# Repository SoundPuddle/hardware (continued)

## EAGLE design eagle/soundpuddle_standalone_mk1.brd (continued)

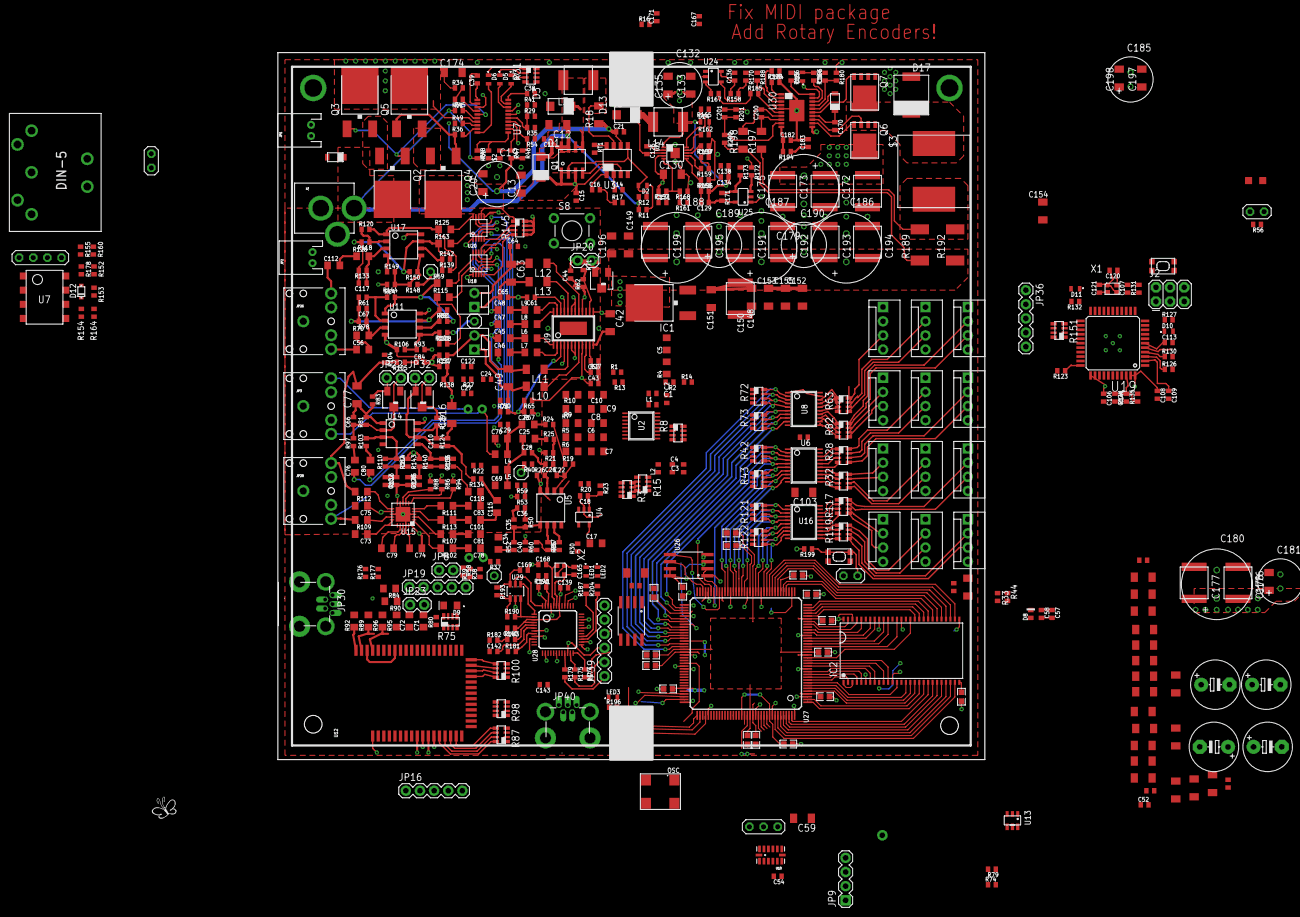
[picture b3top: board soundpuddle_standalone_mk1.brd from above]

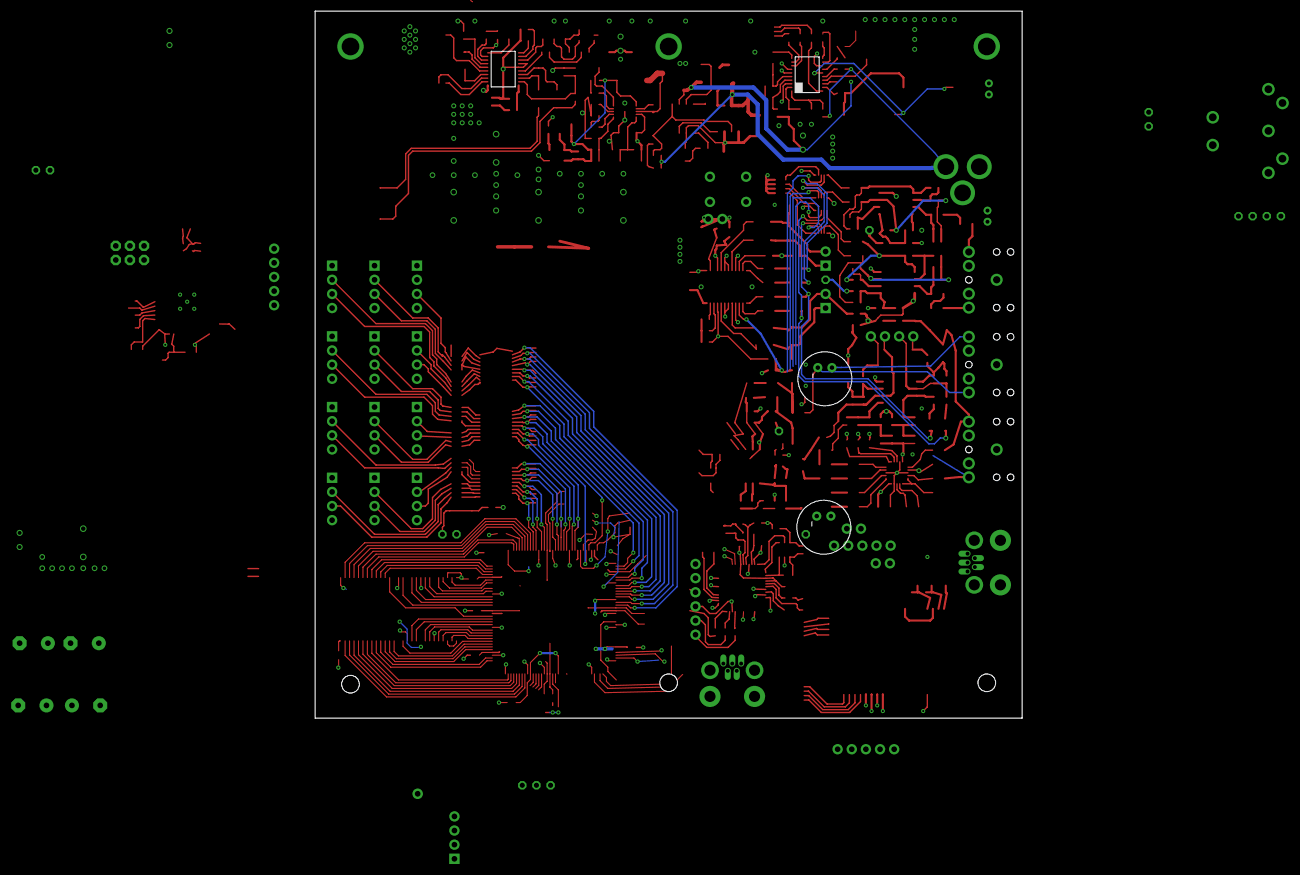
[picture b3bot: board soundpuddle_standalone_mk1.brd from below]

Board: 4 copper layers, 127.0 x 127.0 mm, 531 parts (2 on the bottom side), 427 nets.

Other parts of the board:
U$3: GADGETFACTORY_LOGO

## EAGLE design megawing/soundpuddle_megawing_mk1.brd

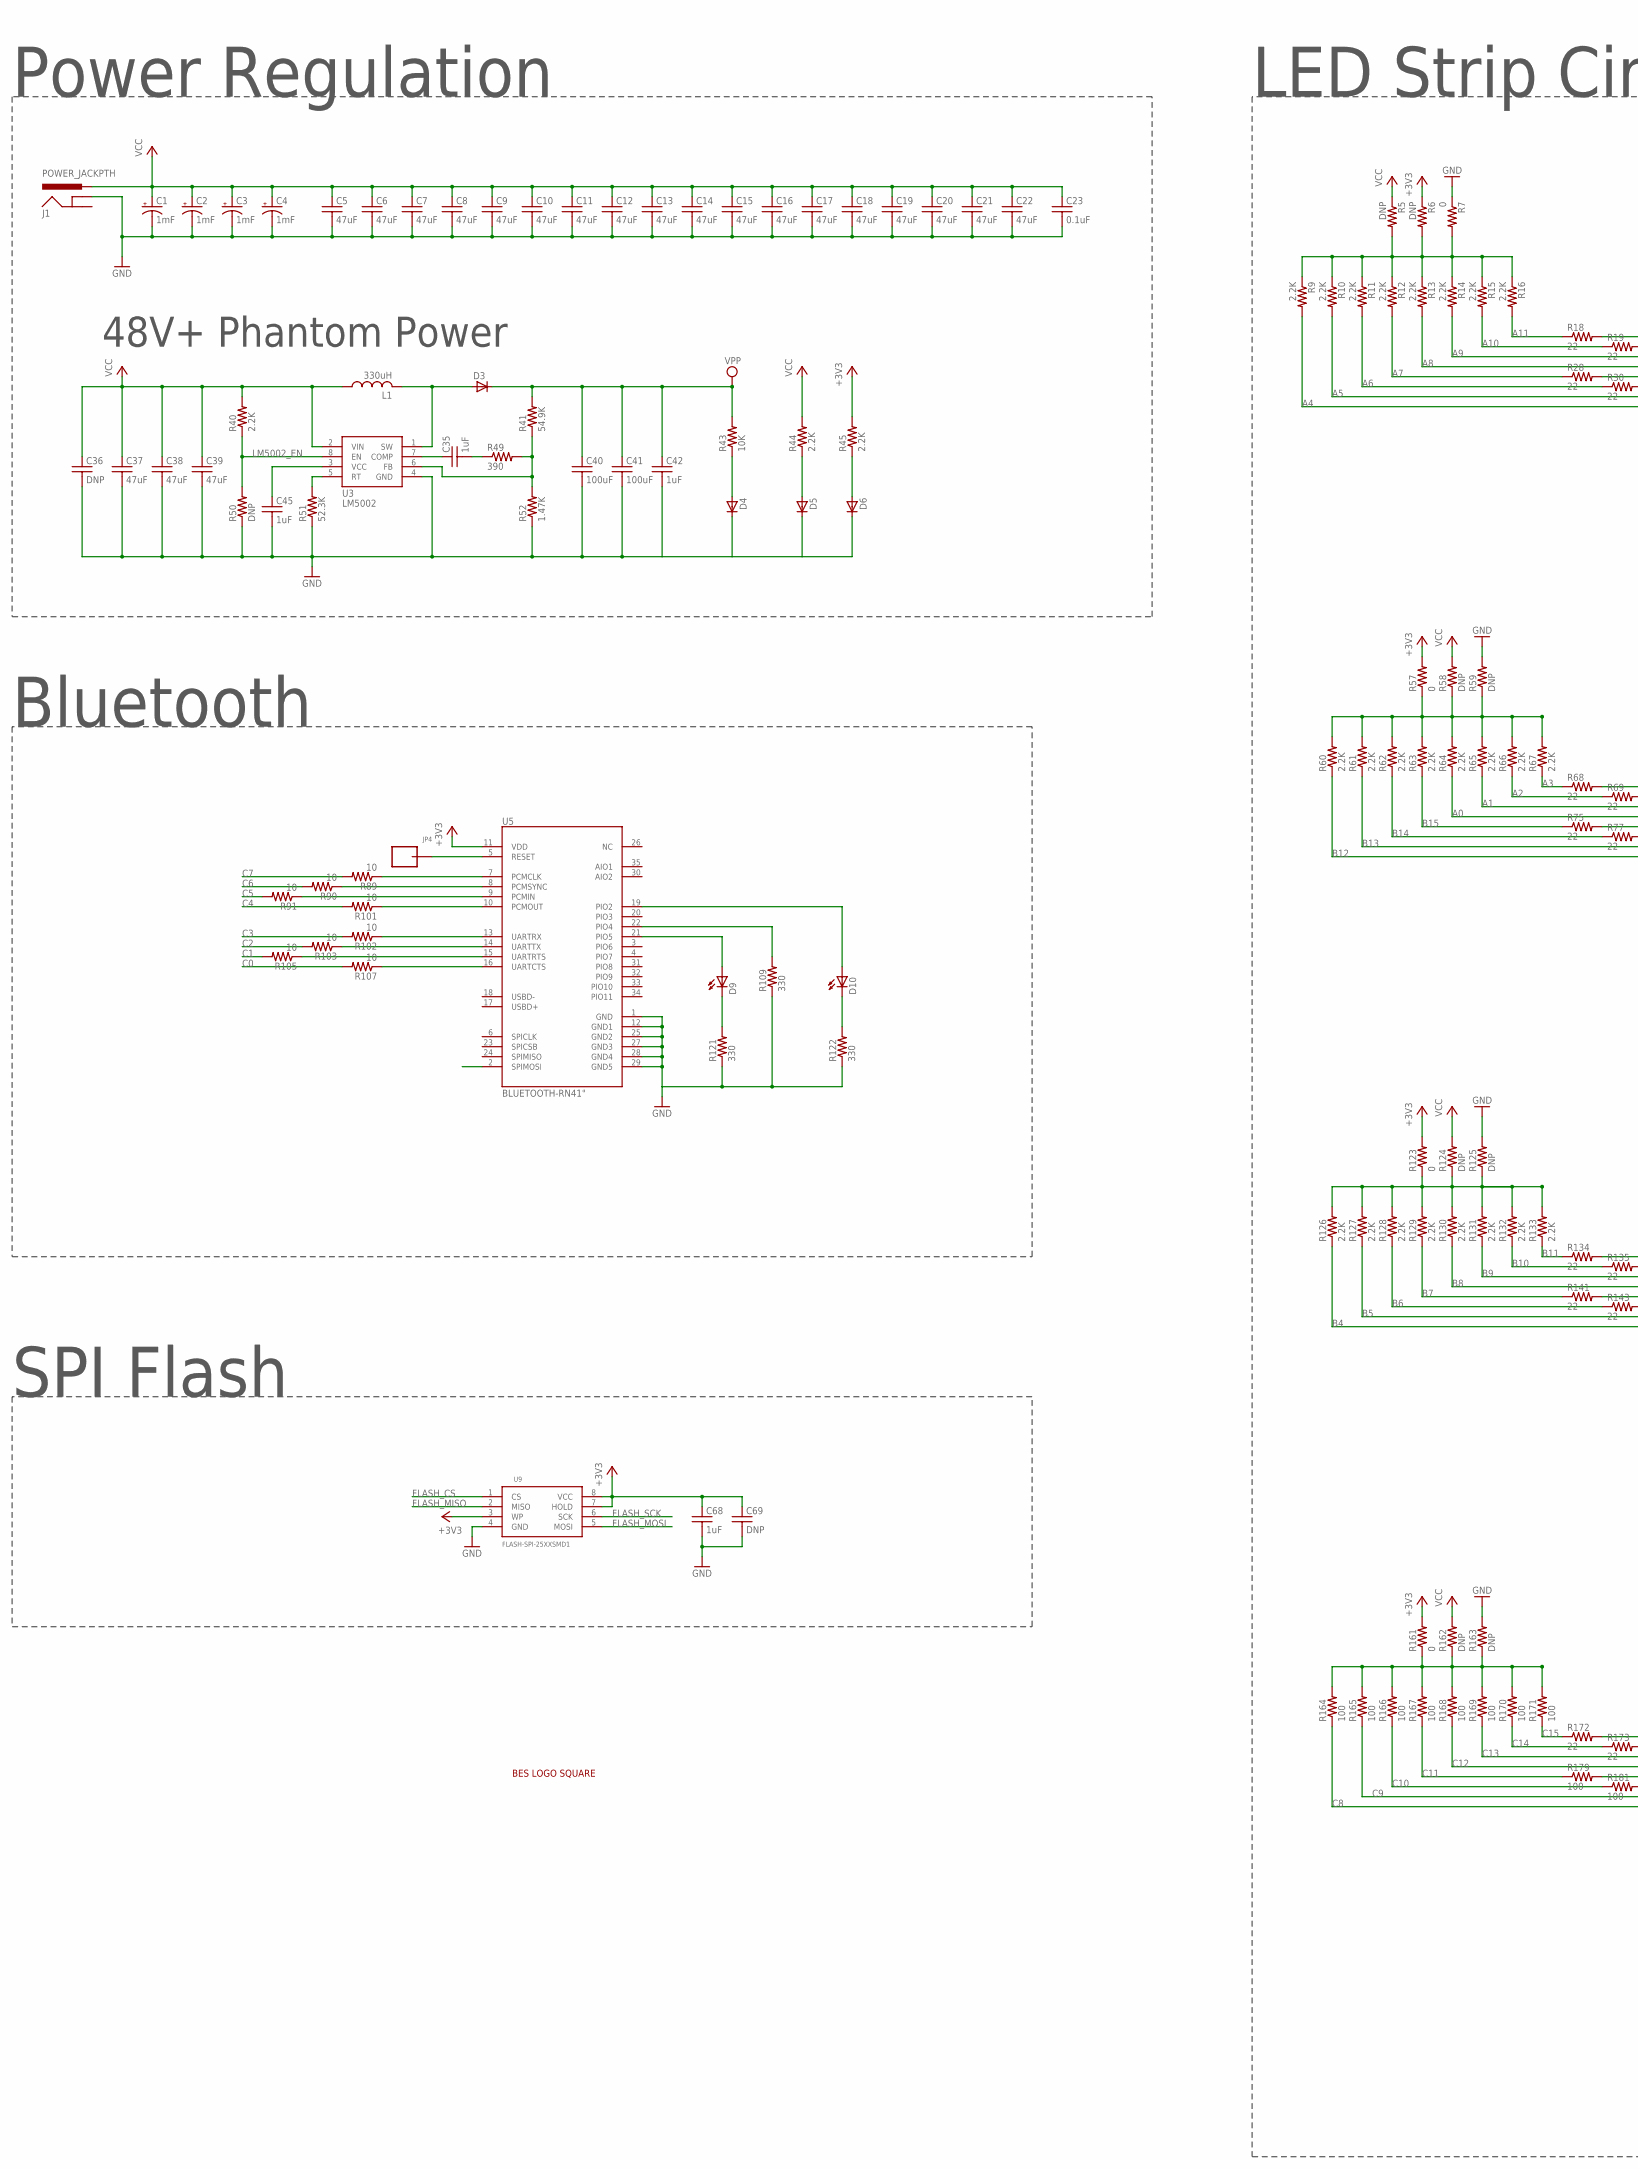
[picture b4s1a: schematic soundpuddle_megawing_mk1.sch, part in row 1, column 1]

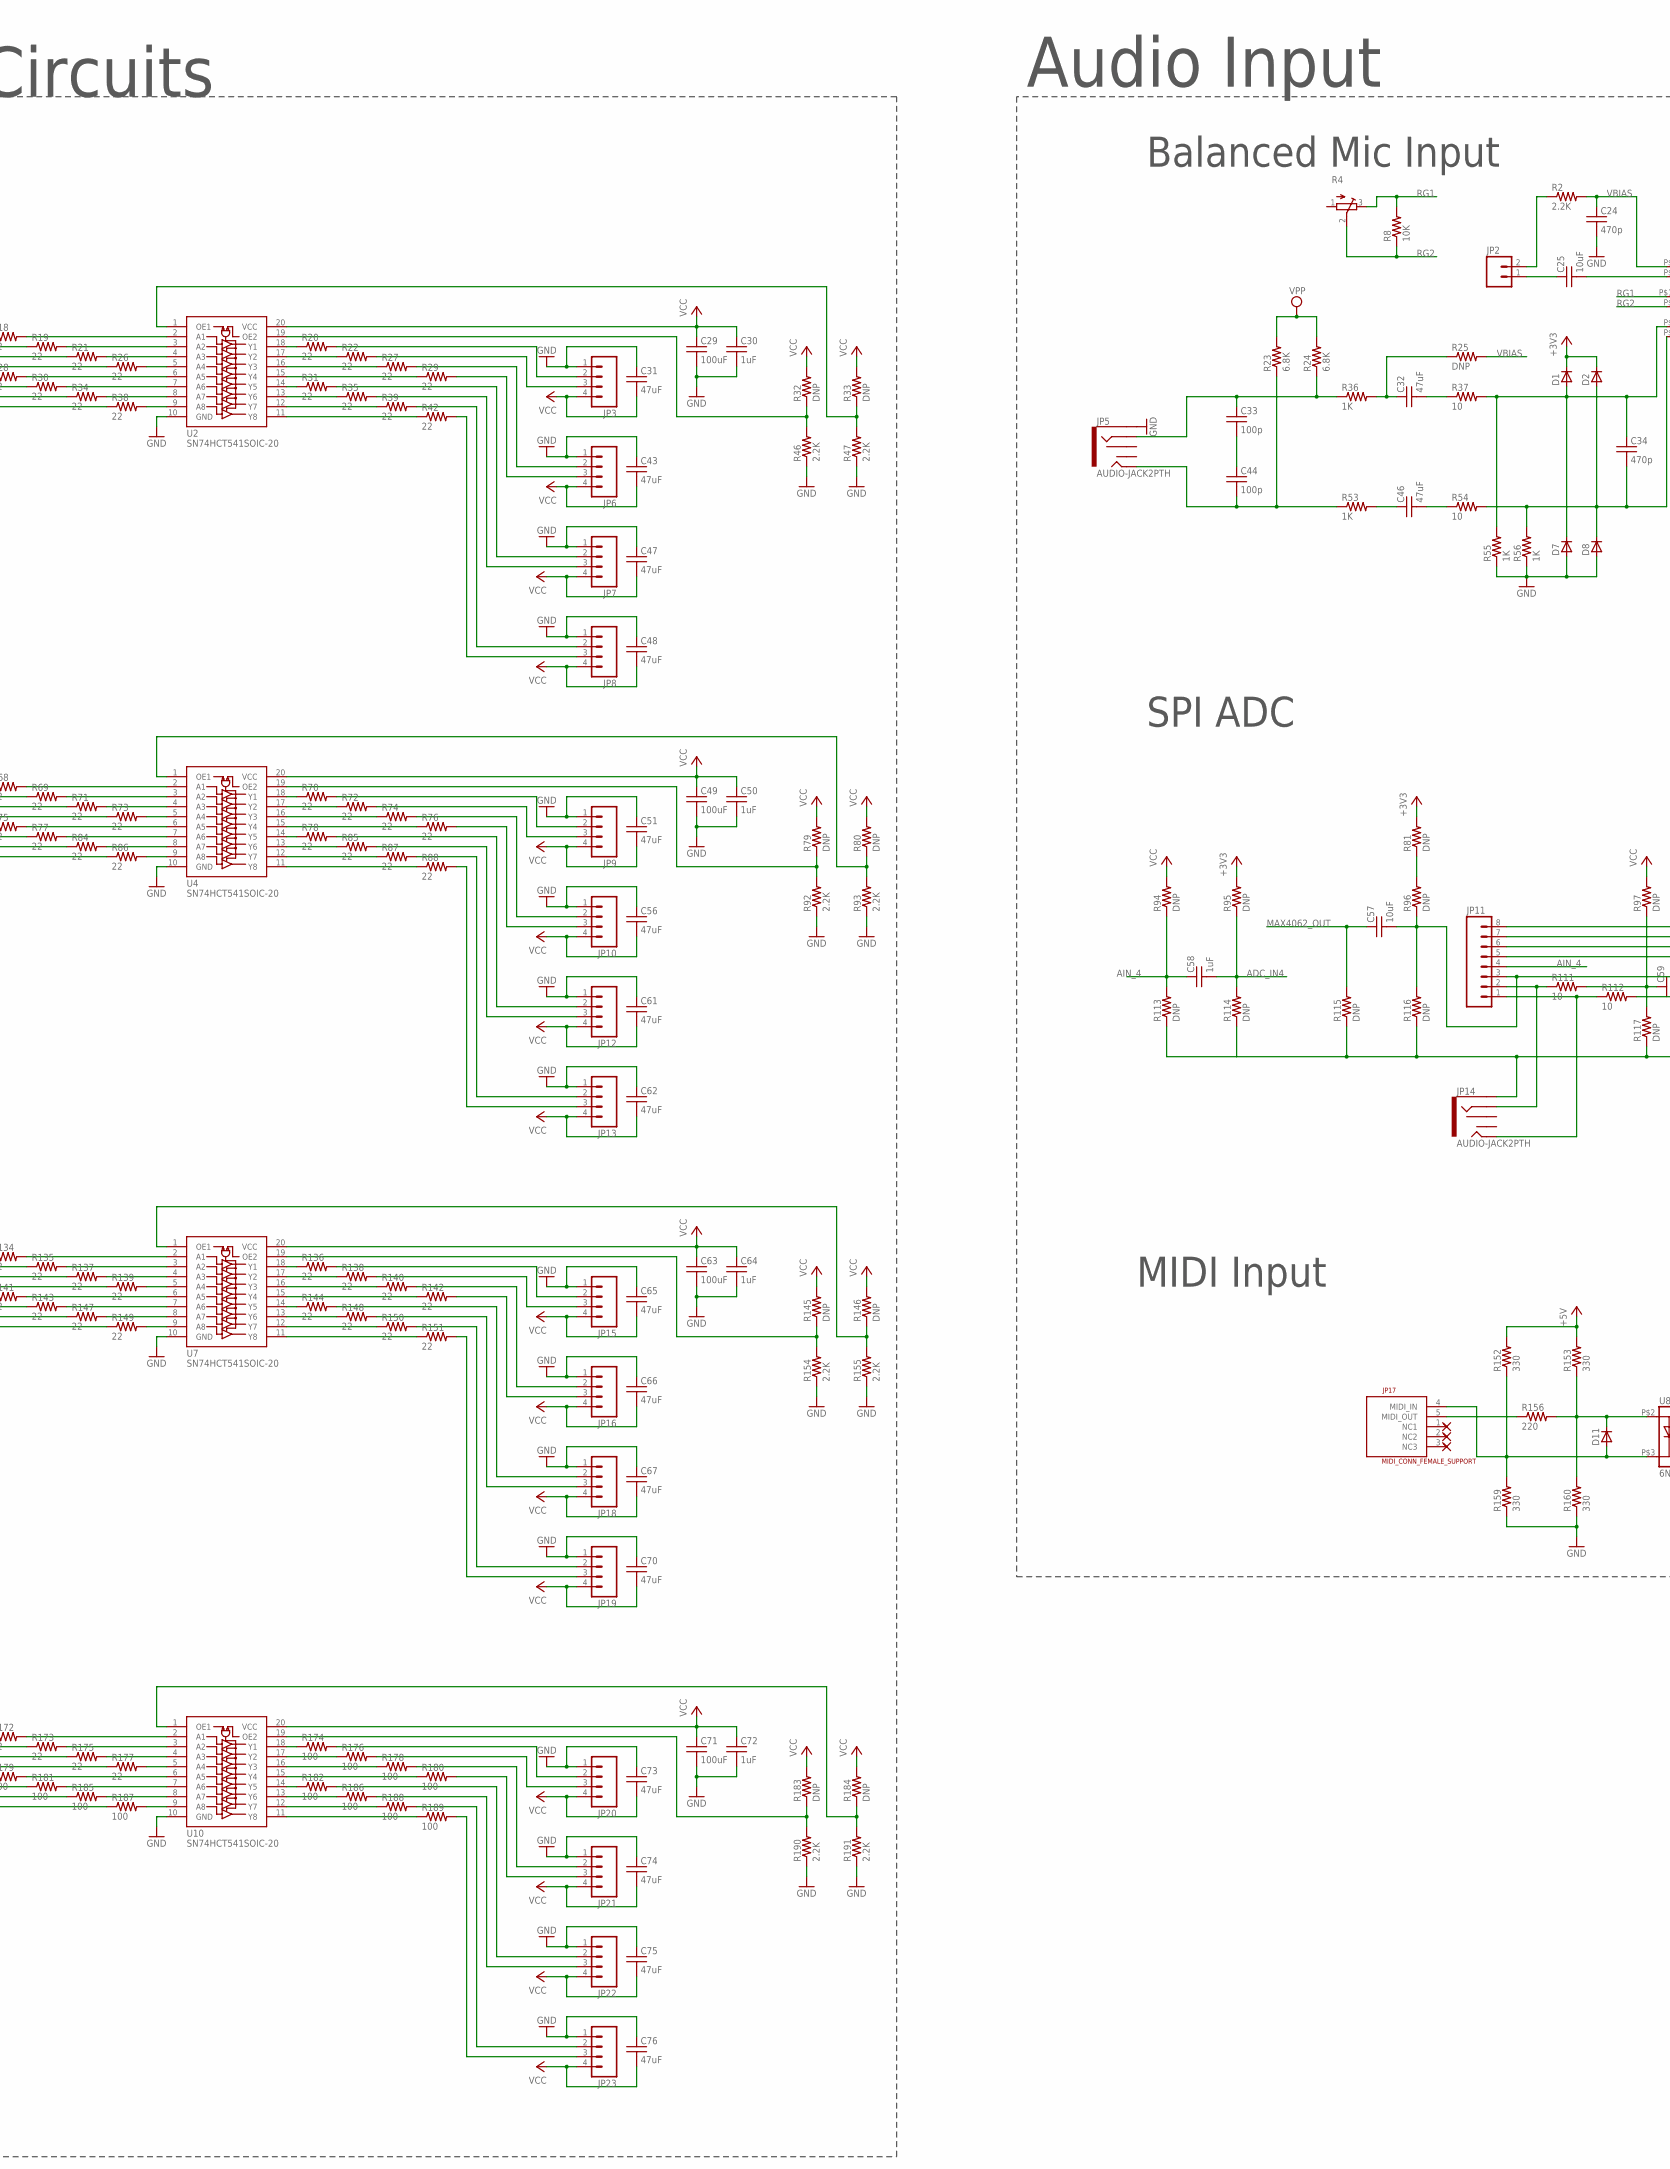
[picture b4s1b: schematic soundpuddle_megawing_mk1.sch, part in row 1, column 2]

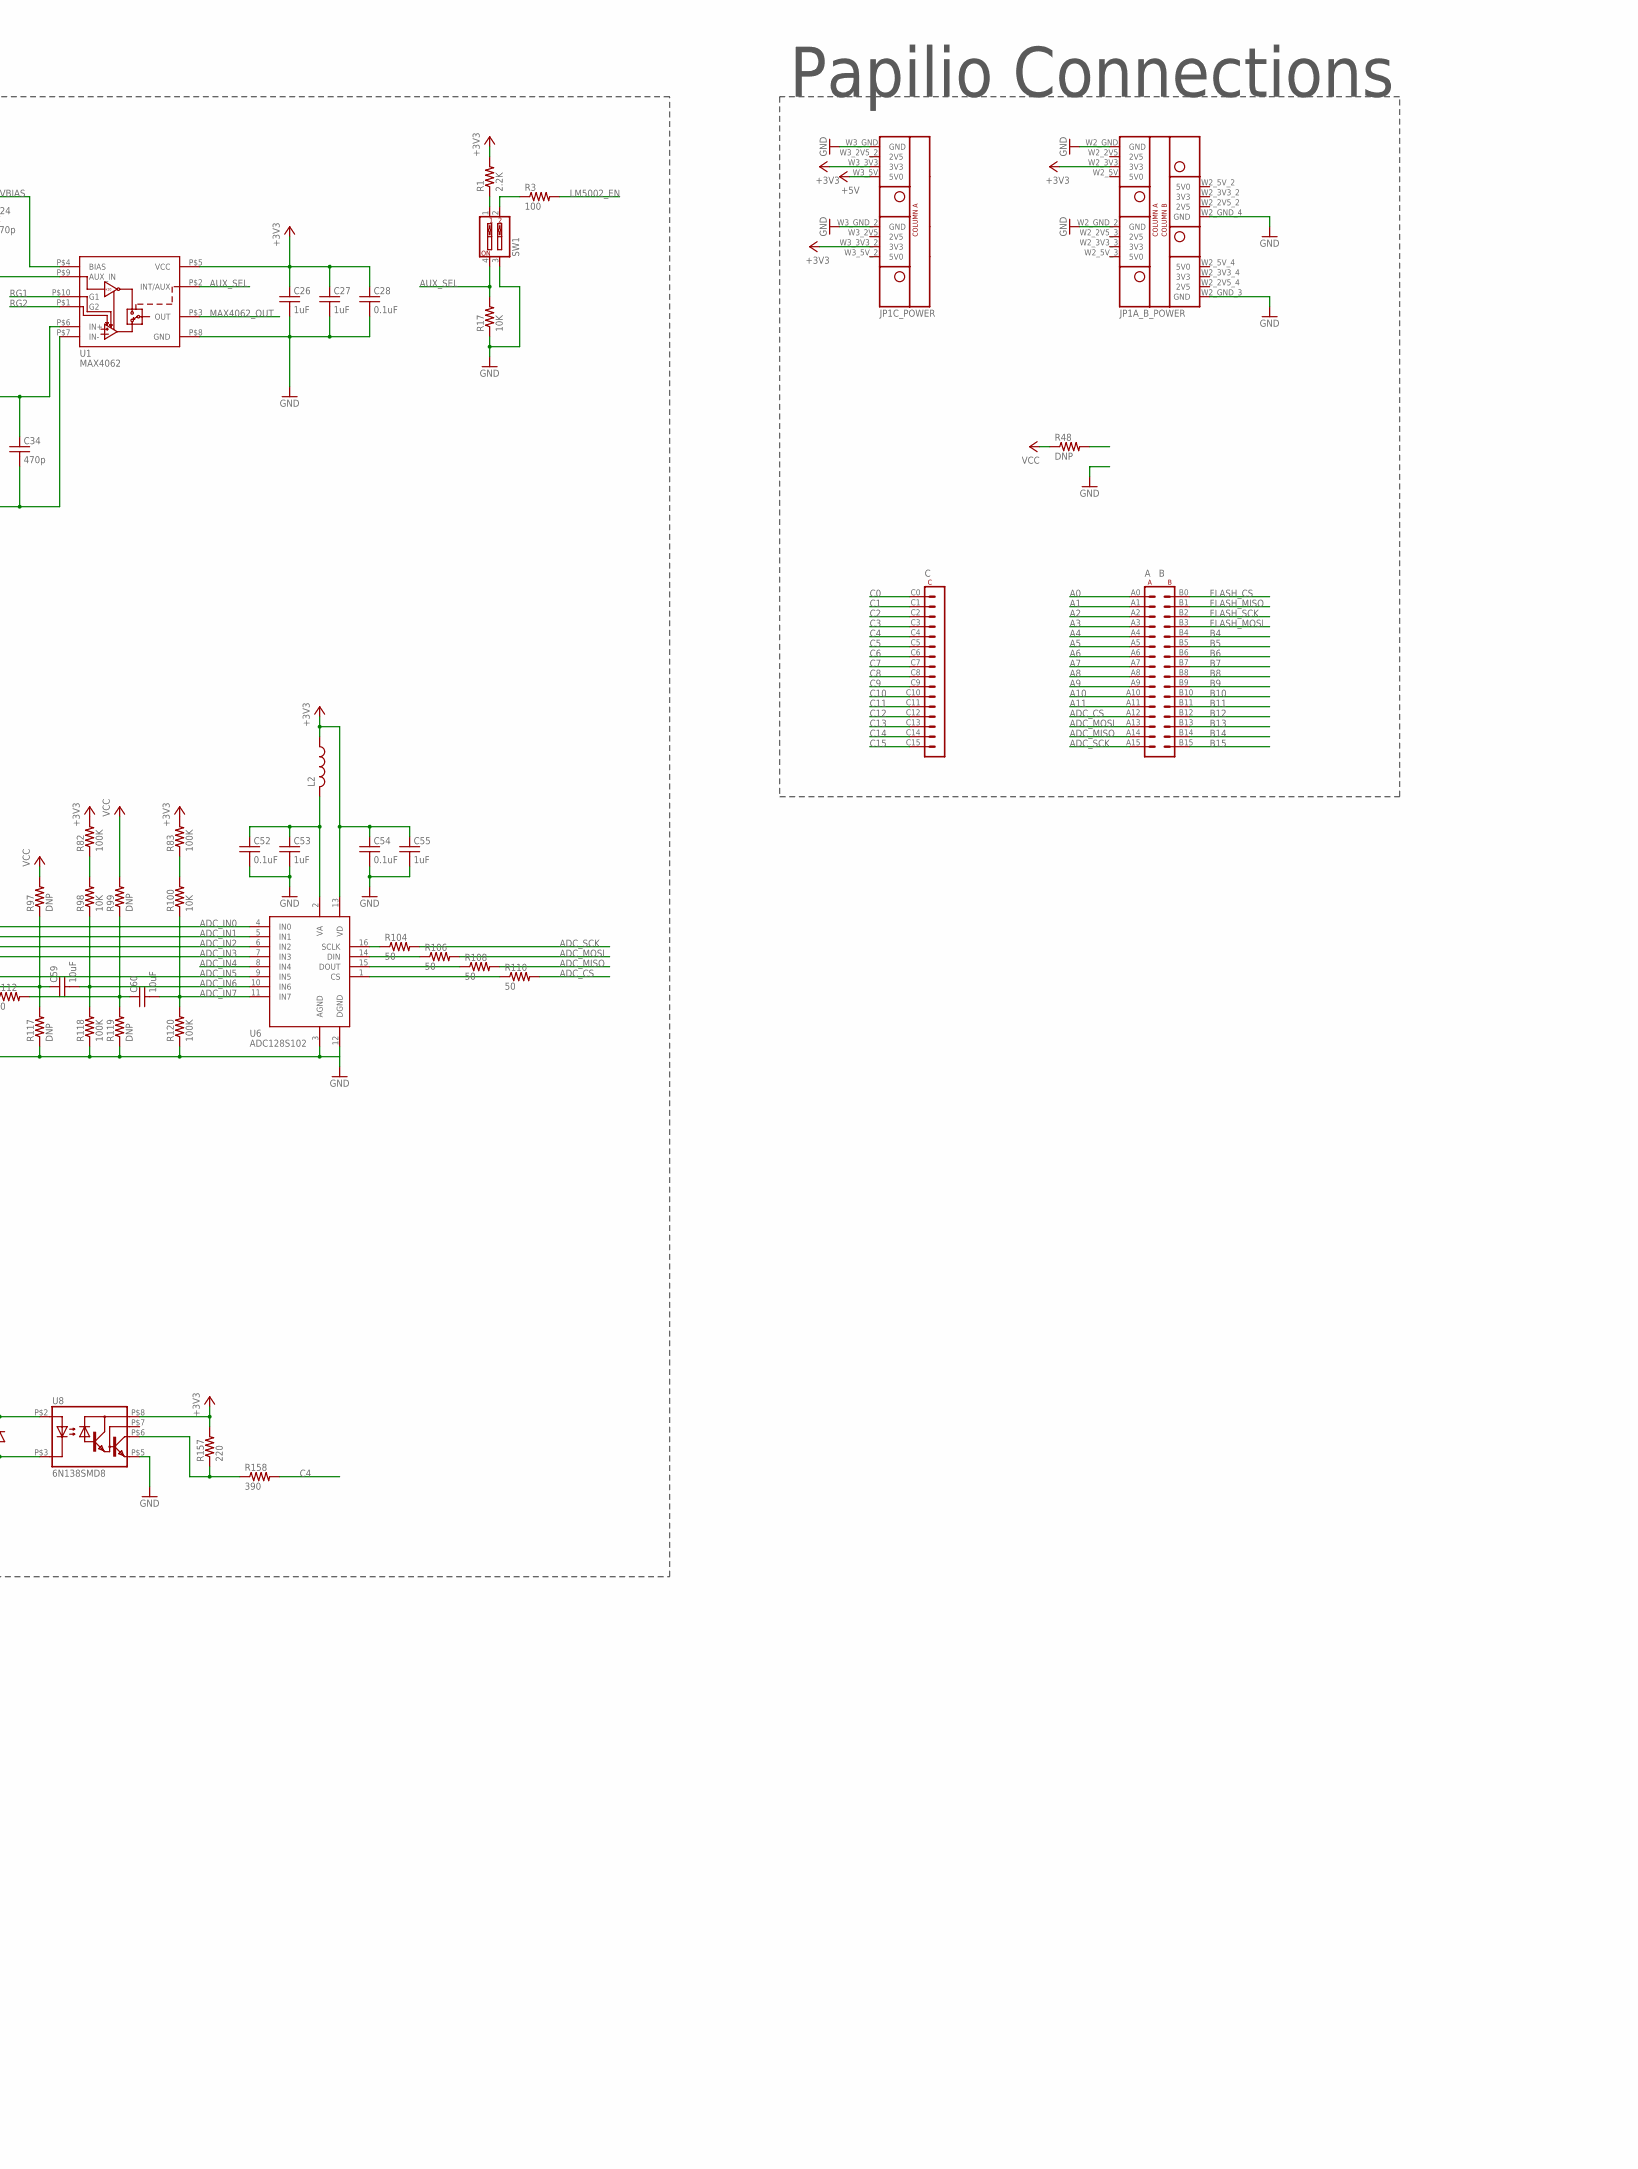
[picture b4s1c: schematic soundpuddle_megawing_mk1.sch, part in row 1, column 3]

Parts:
C1, C2, C3, C4: 1mF; E5-8,5
C5, C6, C7, C8, C9, C10, C11, C12, C13, C14, C15, C16, C17, C18, C19, C20, C21, C22, C31, C32, C37, C38, C39, C43, C46, C47, C48, C51, C56, C61, C62, C65, C66, C67, C70, C73, C74, C75, C76: 47uF; 1206
C23, C28, C52, C54: 0.1uF; 0603
C24, C34: 470p; 0603
C25, C57, C59, C60: 10uF; 0603
C26, C27, C30, C35, C42, C45, C50, C53, C55, C58, C64, C68, C72: 1uF; 0603
C29, C40, C41, C49, C63, C71: 100uF; 1206
C33, C44: 100p; 0603
C36: DNP; 0603
C69: DNP; 1206
D1, D2, D3, D4, D5, D6, D7, D8, D11: DIODE_SMDSOD-323; SOD-323
D9, D10: LED0805; LED_0805
J1: POWER_JACKPTH; POWER_JACK_PTH
JP1: PAPILIO_PLUS_MEGAWING; PAPILIO_PLUS
JP2: M02PTH; 1X02
JP3, JP6, JP7, JP8, JP9, JP10, JP12, JP13, JP15, JP16, JP18, JP19, JP20, JP21, JP22, JP23: M04POLAR; MOLEX-1X4
JP4: HEADER-SMALL-1PIN; HEADER-SMALL-1PIN-0.036IN
JP5, JP14: AUDIO-JACK2PTH; AUDIO-JACK
JP11: M081X08; 1X08
JP17: MIDI_CONN_FEMALE_SUPPORT; DIN_5_FEMALE_SUPPORT
L1: 330uH; INDUCTOR_10X10MM
L2: INDUCTOR0603; 0603
LOGO1: LOGO
R1, R2, R9, R10, R11, R12, R13, R14, R15, R16, R40, R44, R45, R46, R47, R60, R61, R62, R63, R64, R65, R66, R67, R92, R93, R126, R127, R128, R129, R130, R131, R132, R133, R154, R155, R190, R191: 2.2K; 0603
R3, R164, R165, R166, R167, R168, R169, R170, R171, R174, R176, R178, R179, R180, R181, R182, R185, R186, R187, R188, R189: 100; 0603
R4: TRIMPOTTC33X; TC33X
R5, R6, R25, R32, R33, R48, R50, R58, R59, R79, R80, R81, R94, R95, R96, R97, R99, R113, R114, R115, R116, R117, R119, R124, R125, R145, R146, R162, R163, R183, R184: DNP; 0603
R7, R57, R123, R161: 0; 0603
R8, R17, R43, R98, R100: 10K; 0603
R18, R19, R20, R21, R22, R26, R27, R28, R29, R30, R31, R34, R35, R38, R39, R42, R68, R69, R70, R71, R72, R73, R74, R75, R76, R77, R78, R84, R85, R86, R87, R88, R134, R135, R136, R137, R138, R139, R140, R141, R142, R143, R144, R147, R148, R149, R150, R151, R172, R173, R175, R177: 22; 0603
R23, R24: 6.8K; 0603
R36, R53, R55, R56: 1K; 0603
R37, R54, R89, R90, R91, R101, R102, R103, R105, R107, R111, R112: 10; 0603
R41: 54.9K; 0603
R49, R158: 390; 0603
R51: 52.3K; 0603
R52: 1.47K; 0603
R82, R83, R118, R120: 100K; 0603
R104, R106, R108, R110: 50; 0603
R109, R121, R122, R152, R153, R159, R160: 330; 0603
R156, R157: 220; 0603
SW1: SW_DIP-2; DIPSWITCH-02
U1: MAX4062; MSOP10
U2, U4, U7, U10: SN74HCT541SOIC-20; SOIC-20
U3: LM5002; SO8
U5: BLUETOOTH-RN41"; RN41
U6: ADC128S102; TSSOP16
U8: 6N138SMD8; SMD-8
U9: FLASH-SPI-25XXSMD1; SO08-EIAJ

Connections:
+3V3: C26.1, C27.1, C28.1, C54.1, C55.1, C68.1, C69.P$1 (1), D1.C, D2.C, JP1.W2_3V3 (3V3), JP1.W3_3V3 (3V3), JP1.W3_3V3_2 (3V3), L2.1, R1.2, R6.1, R45.2, R57.2, R81.2, R82.2, R83.2, R95.2, R123.2, R157.2, R161.2, U1.P$5 (VCC), U5.11 (VDD), U6.13 (VD), U8.P$8 (VCC), U9.3 (WP), U9.7 (HOLD), U9.8 (VCC)
+5V: JP1.W3_5V (5V0), R152.2, R153.2
A0: JP1.A0, R64.1, R73.1
A1: JP1.A1, R65.1, R71.1
A2: JP1.A2, R66.1, R69.1
A3: JP1.A3, R67.1, R68.1
A4: JP1.A4, R9.2, R38.1
A5: JP1.A5, R10.2, R34.1
A6: JP1.A6, R11.2, R30.1
A7: JP1.A7, R12.2, R28.1
A8: JP1.A8, R13.2, R26.1
A9: JP1.A9, R14.2, R21.1
A10: JP1.A10, R15.2, R19.1
A11: JP1.A11, R16.2, R18.1
ADC_CS: JP1.A12, R110.2
ADC_IN0: JP11.8, U6.4 (IN0)
ADC_IN1: JP11.7, U6.5 (IN1)
ADC_IN2: JP11.6, U6.6 (IN2)
ADC_IN3: JP11.5, U6.7 (IN3)
ADC_IN4: C58.2, R95.1, R114.2, U6.8 (IN4)
ADC_IN5: C57.2, JP11.3, R96.1, R116.2, U6.9 (IN5)
ADC_IN6: C59.2, R98.1, R118.2, U6.10 (IN6)
ADC_IN7: C60.2, R100.1, R120.2, U6.11 (IN7)
ADC_MISO: JP1.A14, R108.2
ADC_MOSI: JP1.A13, R106.2
ADC_SCK: JP1.A15, R104.2
AIN_4: C58.1, JP11.4, R94.1, R113.2
AUX_SEL: R17.2, SW1.4, U1.P$2 (INT/AUX)
B4: JP1.B4, R126.1, R149.1
B5: JP1.B5, R127.1, R147.1
B6: JP1.B6, R128.1, R143.1
B7: JP1.B7, R129.1, R141.1
B8: JP1.B8, R130.1, R139.1
B9: JP1.B9, R131.1, R137.1
B10: JP1.B10, R132.1, R135.1
B11: JP1.B11, R133.1, R134.1
B12: JP1.B12, R60.1, R86.1
B13: JP1.B13, R61.1, R84.1
B14: JP1.B14, R62.1, R77.1
B15: JP1.B15, R63.1, R75.1
C0: JP1.C0, R107.2
C1: JP1.C1, R105.2
C2: JP1.C2, R103.2
C3: JP1.C3, R102.2
C4: JP1.C4, R101.2, R158.2
C5: JP1.C5, R91.2
C6: JP1.C6, R90.2
C7: JP1.C7, R89.2
C8: JP1.C8, R164.1, R187.1
C9: JP1.C9, R165.1, R185.1
C10: JP1.C10, R166.1, R181.1
C11: JP1.C11, R167.1, R179.1
C12: JP1.C12, R168.1, R177.1
C13: JP1.C13, R169.1, R175.1
C14: JP1.C14, R170.1, R173.1
C15: JP1.C15, R171.1, R172.1
FLASH_CS: JP1.B0, U9.1 (CS)
FLASH_MISO: JP1.B1, U9.2 (MISO)
FLASH_MOSI: JP1.B3, U9.5 (MOSI)
FLASH_SCK: JP1.B2, U9.6 (SCK)
GND: C1.-, C2.-, C3.-, C4.-, C5.P$2 (2), C6.P$2 (2), C7.P$2 (2), C8.P$2 (2), C9.P$2 (2), C10.P$2 (2), C11.P$2 (2), C12.P$2 (2), C13.P$2 (2), C14.P$2 (2), C15.P$2 (2), C16.P$2 (2), C17.P$2 (2), C18.P$2 (2), C19.P$2 (2), C20.P$2 (2), C21.P$2 (2), C22.P$2 (2), C23.2, C24.2, C26.2, C27.2, C28.2, C29.P$2 (2), C30.2, C31.P$1 (1), C36.2, C37.P$2 (2), C38.P$2 (2), C39.P$2 (2), C40.P$2 (2), C41.P$2 (2), C42.2, C43.P$1 (1), C45.2, C47.P$1 (1), C48.P$1 (1), C49.P$2 (2), C50.2, C51.P$1 (1), C52.2, C53.2, C54.2, C55.2, C56.P$1 (1), C61.P$1 (1), C62.P$1 (1), C63.P$2 (2), C64.2, C65.P$1 (1), C66.P$1 (1), C67.P$1 (1), C68.2, C69.P$2 (2), C70.P$1 (1), C71.P$2 (2), C72.2, C73.P$1 (1), C74.P$1 (1), C75.P$1 (1), C76.P$1 (1), D4.C, D5.C, D6.C, D7.A, D8.A, J1.GNDBREAK, JP1.W2_GND (GND), JP1.W2_GND_2 (GND), JP1.W2_GND_3 (GND), JP1.W2_GND_4 (GND), JP1.W3_GND (GND), JP1.W3_GND_2 (GND), JP3.1, JP5.SLEEVE, JP6.1, JP7.1, JP8.1, JP9.1, JP10.1, JP12.1, JP13.1, JP14.SLEEVE, JP15.1, JP16.1, JP18.1, JP19.1, JP20.1, JP21.1, JP22.1, JP23.1, R7.1, R17.1, R46.1, R47.1, R50.1, R51.1, R52.1, R55.1, R56.1, R59.2, R92.1, R93.1, R109.1, R113.1, R114.1, R115.1, R116.1, R117.1, R118.1, R119.1, R120.1, R121.1, R122.1, R125.2, R154.1, R155.1, R159.1, R160.1, R163.2, R190.1, R191.1, SW1.3, U1.P$8 (GND), U2.10 (GND), U3.4 (GND), U4.10 (GND), U5.1 (GND), U5.12 (GND1), U5.25 (GND2), U5.27 (GND3), U5.28 (GND4), U5.29 (GND5), U6.3 (AGND), U6.12 (DGND), U7.10 (GND), U8.P$5 (GND), U9.4 (GND), U10.10 (GND)
LM5002_EN: R3.2, R40.1, R50.2, U3.8 (EN)
MAX4062_OUT: C57.1, R115.2, U1.P$3 (OUT)
unnamed: C52.1, C53.1, L2.2, U6.2 (VA)
unnamed: R107.1, U5.16 (UARTCTS)
unnamed: JP2.2, R2.1
unnamed: C25.1, JP2.1
unnamed: R105.1, U5.15 (UARTRTS)
unnamed: R103.1, U5.14 (UARTTX)
unnamed: C46.P$1 (1), R53.2
unnamed: C44.2, JP5.TIP, R23.1, R53.1
unnamed: C33.2, C44.1
unnamed: C32.P$1 (1), R25.1, R36.2
unnamed: R102.1, U5.13 (UARTRX)
unnamed: R104.1, U6.16 (SCLK)
unnamed: R106.1, U6.14 (DIN)
unnamed: R110.1, U6.1 (CS)
unnamed: R108.1, U6.15 (DOUT)
unnamed: D9.2 (C), R121.2
unnamed: D10.2 (C), R122.2
unnamed: D10.1 (A), U5.19 (PIO2)
unnamed: D9.1 (A), U5.21 (PIO5)
unnamed: D3.A, L1.P$2 (2), U3.1 (SW)
unnamed: R109.2, U5.22 (PIO4)
unnamed: JP20.3, R176.2
unnamed: R1.1, SW1.1
unnamed: R33.1, R47.2, U2.1 (OE1)
unnamed: R5.2, R6.2, R7.2, R9.1, R10.1, R11.1, R12.1, R13.1, R14.1, R15.1, R16.1
unnamed: C32.P$2 (2), R37.1
unnamed: C46.P$2 (2), R54.1
unnamed: D4.A, R43.1
unnamed: D5.A, R44.1
unnamed: R81.1, R96.2
unnamed: R82.1, R98.2
unnamed: JP11.2, JP14.RING, R111.1
unnamed: R83.1, R100.2
unnamed: JP11.1, JP14.TIP, R112.1
unnamed: C60.1, R99.1, R112.2, R119.2
unnamed: C59.1, R97.1, R111.2, R117.2
unnamed: R3.1, SW1.2
unnamed: R161.1, R162.1, R163.1, R164.2, R165.2, R166.2, R167.2, R168.2, R169.2, R170.2, R171.2
unnamed: R101.1, U5.10 (PCMOUT)
unnamed: D6.A, R45.1
unnamed: R79.1, R92.2, U4.19 (OE2)
unnamed: R145.1, R154.2, U7.19 (OE2)
unnamed: R184.1, R191.2, U10.1 (OE1)
unnamed: R91.1, U5.9 (PCMIN)
unnamed: R90.1, U5.8 (PCMSYNC)
unnamed: R89.1, U5.7 (PCMCLK)
unnamed: R183.1, R190.2, U10.19 (OE2)
unnamed: JP4.P$1, U5.5 (RESET)
unnamed: JP17.5 (MIDI_OUT), R156.1
unnamed: D11.C, R153.1, R156.2, R160.2, U8.P$2 (A)
unnamed: D11.A, JP17.4 (MIDI_IN), R152.1, R159.2, U8.P$3 (C)
unnamed: R32.1, R46.2, U2.19 (OE2)
unnamed: R19.2, U2.3 (A2)
unnamed: R26.2, U2.5 (A4)
unnamed: R18.2, U2.2 (A1)
unnamed: R157.1, R158.1, U8.P$6 (VO)
unnamed: R21.2, U2.4 (A3)
unnamed: R28.2, U2.6 (A5)
unnamed: R30.2, U2.7 (A6)
unnamed: R34.2, U2.8 (A7)
unnamed: R38.2, U2.9 (A8)
unnamed: R31.1, U2.14 (Y5)
unnamed: R20.1, U2.18 (Y1)
unnamed: R22.1, U2.17 (Y2)
unnamed: R27.1, U2.16 (Y3)
unnamed: R29.1, U2.15 (Y4)
unnamed: R35.1, U2.13 (Y6)
unnamed: R39.1, U2.12 (Y7)
unnamed: R42.1, U2.11 (Y8)
unnamed: JP7.2, R31.2
unnamed: JP7.3, R35.2
unnamed: JP8.2, R39.2
unnamed: JP8.3, R42.2
unnamed: JP6.3, R29.2
unnamed: JP6.2, R27.2
unnamed: JP3.3, R22.2
unnamed: JP3.2, R20.2
unnamed: JP13.2, R87.2
unnamed: R51.2, U3.5 (RT)
unnamed: C45.1, U3.3 (VCC)
unnamed: C35.1, U3.7 (COMP)
unnamed: R41.1, R49.2, R52.2, U3.6 (FB)
unnamed: C35.2, R49.1
unnamed: C34.2, D2.A, D8.C, R54.2, R56.2, U1.P$7 (IN-)
unnamed: C25.2, U1.P$9 (AUX_IN)
unnamed: R80.1, R93.2, U4.1 (OE1)
unnamed: C33.1, JP5.RING, R24.1, R36.1
unnamed: C34.1, D1.A, D7.C, R37.2, R55.2, U1.P$6 (IN+)
unnamed: R68.2, U4.2 (A1)
unnamed: R69.2, U4.3 (A2)
unnamed: R73.2, U4.5 (A4)
unnamed: R71.2, U4.4 (A3)
unnamed: R75.2, U4.6 (A5)
unnamed: R77.2, U4.7 (A6)
unnamed: R84.2, U4.8 (A7)
unnamed: R86.2, U4.9 (A8)
unnamed: R57.1, R58.1, R59.1, R60.2, R61.2, R62.2, R63.2, R64.2, R65.2, R66.2, R67.2
unnamed: R78.1, U4.14 (Y5)
unnamed: R70.1, U4.18 (Y1)
unnamed: R72.1, U4.17 (Y2)
unnamed: R74.1, U4.16 (Y3)
unnamed: R76.1, U4.15 (Y4)
unnamed: R85.1, U4.13 (Y6)
unnamed: R87.1, U4.12 (Y7)
unnamed: R88.1, U4.11 (Y8)
unnamed: JP12.2, R78.2
unnamed: JP12.3, R85.2
unnamed: JP13.3, R88.2
unnamed: JP23.2, R188.2
unnamed: JP10.3, R76.2
unnamed: JP10.2, R74.2
unnamed: JP9.3, R72.2
unnamed: JP9.2, R70.2
unnamed: R146.1, R155.2, U7.1 (OE1)
unnamed: R134.2, U7.2 (A1)
unnamed: R135.2, U7.3 (A2)
unnamed: R139.2, U7.5 (A4)
unnamed: R137.2, U7.4 (A3)
unnamed: R141.2, U7.6 (A5)
unnamed: R143.2, U7.7 (A6)
unnamed: R147.2, U7.8 (A7)
unnamed: R149.2, U7.9 (A8)
unnamed: R123.1, R124.1, R125.1, R126.2, R127.2, R128.2, R129.2, R130.2, R131.2, R132.2, R133.2
unnamed: R144.1, U7.14 (Y5)
unnamed: R136.1, U7.18 (Y1)
unnamed: R138.1, U7.17 (Y2)
unnamed: R140.1, U7.16 (Y3)
unnamed: R142.1, U7.15 (Y4)
unnamed: R148.1, U7.13 (Y6)
unnamed: R150.1, U7.12 (Y7)
unnamed: R151.1, U7.11 (Y8)
unnamed: JP18.2, R144.2
unnamed: JP18.3, R148.2
unnamed: JP19.2, R150.2
unnamed: JP19.3, R151.2
unnamed: JP16.3, R142.2
unnamed: JP16.2, R140.2
unnamed: JP15.3, R138.2
unnamed: JP15.2, R136.2
unnamed: R172.2, U10.2 (A1)
unnamed: R173.2, U10.3 (A2)
unnamed: R177.2, U10.5 (A4)
unnamed: R175.2, U10.4 (A3)
unnamed: R179.2, U10.6 (A5)
unnamed: R181.2, U10.7 (A6)
unnamed: R185.2, U10.8 (A7)
unnamed: R187.2, U10.9 (A8)
unnamed: R182.1, U10.14 (Y5)
unnamed: R174.1, U10.18 (Y1)
unnamed: R176.1, U10.17 (Y2)
unnamed: R178.1, U10.16 (Y3)
unnamed: R180.1, U10.15 (Y4)
unnamed: R186.1, U10.13 (Y6)
unnamed: R188.1, U10.12 (Y7)
unnamed: R189.1, U10.11 (Y8)
unnamed: JP22.2, R182.2
unnamed: JP22.3, R186.2
unnamed: JP23.3, R189.2
unnamed: JP21.3, R180.2
unnamed: JP21.2, R178.2
unnamed: JP20.2, R174.2
RG1: R4.3 (E), R8.2, U1.P$10 (G1)
RG2: R4.2 (S), R8.1, U1.P$1 (G2)
VBIAS: C24.1, R2.2, R25.2, U1.P$4 (BIAS)
VCC: C1.+, C2.+, C3.+, C4.+, C5.P$1 (1), C6.P$1 (1), C7.P$1 (1), C8.P$1 (1), C9.P$1 (1), C10.P$1 (1), C11.P$1 (1), C12.P$1 (1), C13.P$1 (1), C14.P$1 (1), C15.P$1 (1), C16.P$1 (1), C17.P$1 (1), C18.P$1 (1), C19.P$1 (1), C20.P$1 (1), C21.P$1 (1), C22.P$1 (1), C23.1, C29.P$1 (1), C30.1, C31.P$2 (2), C36.1, C37.P$1 (1), C38.P$1 (1), C39.P$1 (1), C43.P$2 (2), C47.P$2 (2), C48.P$2 (2), C49.P$1 (1), C50.1, C51.P$2 (2), C56.P$2 (2), C61.P$2 (2), C62.P$2 (2), C63.P$1 (1), C64.1, C65.P$2 (2), C66.P$2 (2), C67.P$2 (2), C70.P$2 (2), C71.P$1 (1), C72.1, C73.P$2 (2), C74.P$2 (2), C75.P$2 (2), C76.P$2 (2), J1.PWR, JP3.4, JP6.4, JP7.4, JP8.4, JP9.4, JP10.4, JP12.4, JP13.4, JP15.4, JP16.4, JP18.4, JP19.4, JP20.4, JP21.4, JP22.4, JP23.4, L1.P$1 (1), R5.1, R32.2, R33.2, R40.2, R44.2, R48.1, R58.2, R79.2, R80.2, R94.2, R97.2, R99.2, R124.2, R145.2, R146.2, R162.2, R183.2, R184.2, U2.20 (VCC), U3.2 (VIN), U4.20 (VCC), U7.20 (VCC), U10.20 (VCC)
VPP: C40.P$1 (1), C41.P$1 (1), C42.1, D3.C, R23.2, R24.2, R41.2, R43.2

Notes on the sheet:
Audio Input
Papilio Connections
LED Strip Circuits
Bluetooth
Power Regulation
SPI Flash
48V+ Phantom Power
MIDI Input
SPI ADC
Balanced Mic Input

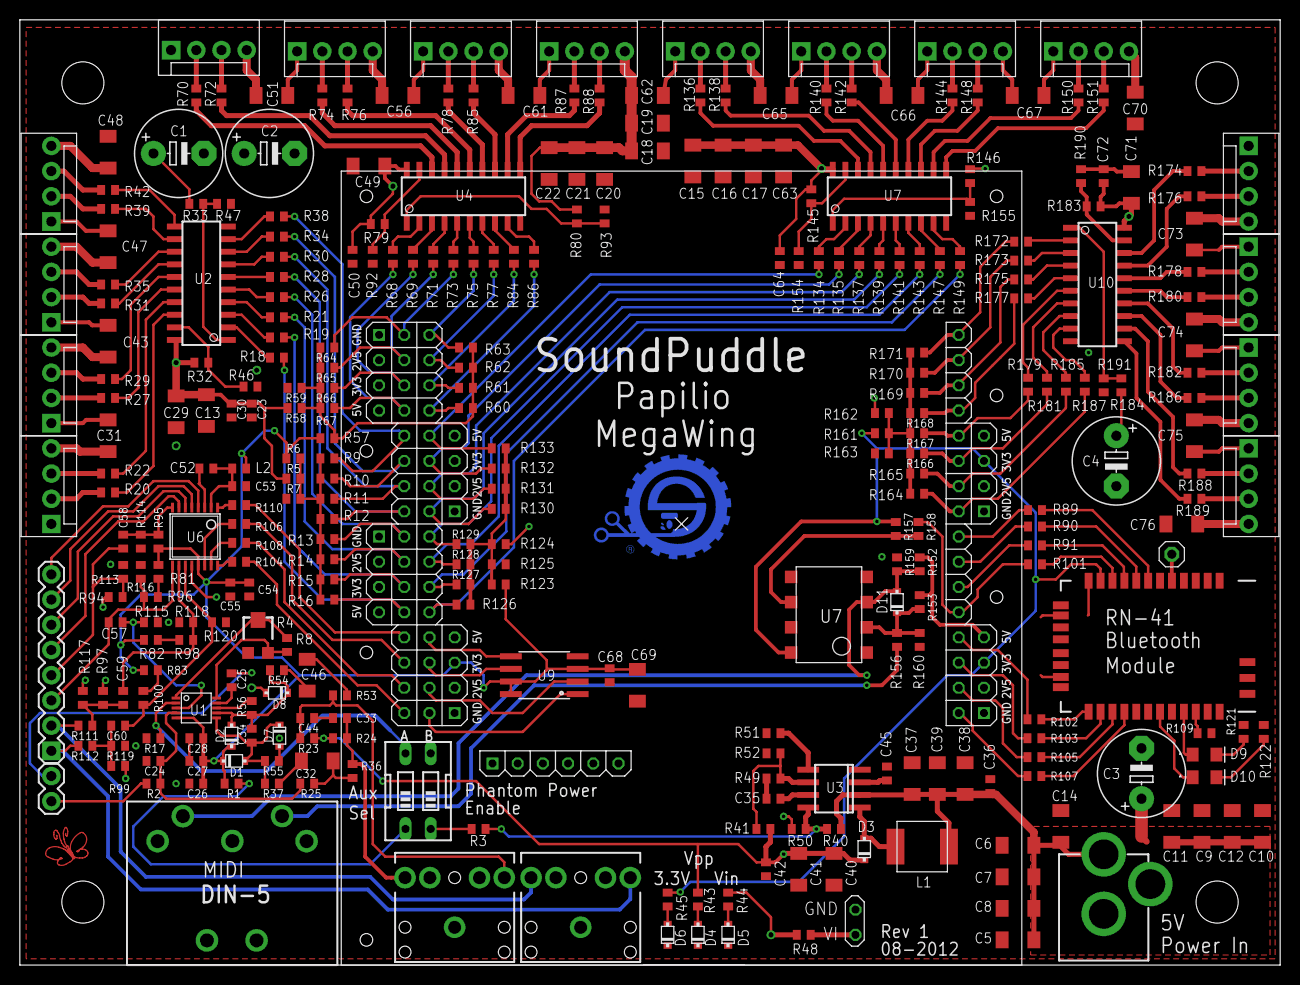
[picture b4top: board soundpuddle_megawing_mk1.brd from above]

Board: 4 copper layers, 127.0 x 95.2 mm, 317 parts (1 on the bottom side), 229 nets.

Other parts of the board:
U$4: BUTTERFLY_LOGO_ON_COPPER

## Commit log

2012-07-30 Initial commit of the eagle files for the SoundPuddle megawing
2013-01-28 adding Soundpuddle standalone PCB eagle files
2013-01-28 adjusting pcb layout image
2013-04-25 added eagle files for the mk2 megawing. These files reflect the ordered PCB
2013-04-25 removing files for the defunct standalone board.
2013-04-25 updating .tsv file for soundpuddle BOM management
2013-05-16 adding experimental linedriver PCB for buffering SPI communication with LED strips
2013-05-16 updated eagle files for the MK2 PCB. Some component values are not yet final, hardware is in initial physical testing phase
